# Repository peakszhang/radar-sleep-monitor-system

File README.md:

# radar-sleep-monitor-system
---
## Project description
### Hardware
- ESP32-S-Wroom MCU
- MR60BHA1 60GHz mmWave Radar Module

### Firmware
- Radar serial interface
- Wifi connection
- MQTT protocol
- Alarm sound (optional)

### Software
- Smartphone display data (from MQTT)
- Phone alarm
- ESP32 smartconfig (https://github.com/EspressifApp/EsptouchForAndroid)
- Cloud server (optional)

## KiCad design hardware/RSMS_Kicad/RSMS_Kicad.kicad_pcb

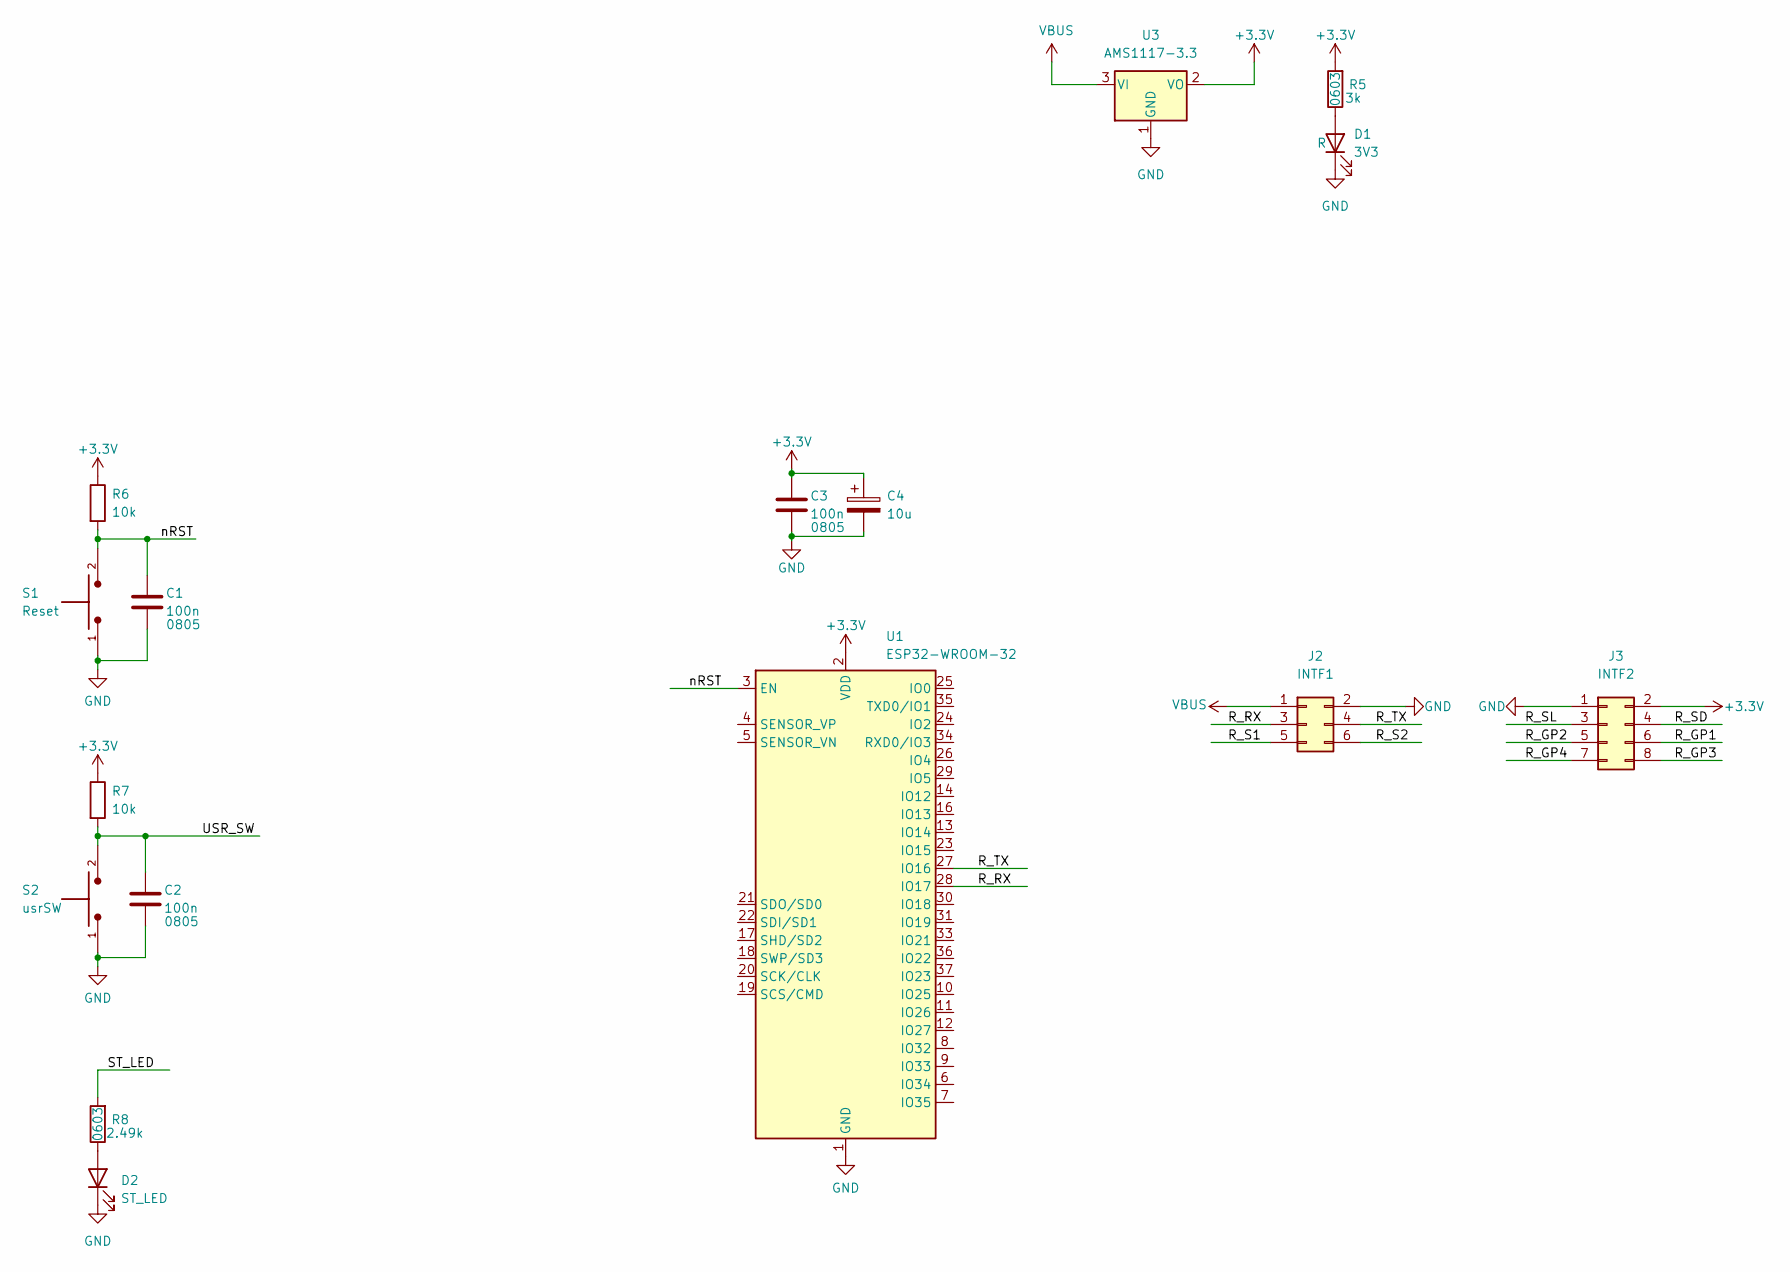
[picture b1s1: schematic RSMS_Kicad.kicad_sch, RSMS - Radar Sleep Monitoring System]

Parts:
C1, C2, C3: 100n; C_0805_2012Metric
C4: 10u; CP_EIA-3216-10_Kemet-I
D1: 3V3; LED_0805_2012Metric
D2: ST_LED; LED_0805_2012Metric
J2: INTF1; PinHeader_2x03_P2.00mm_Vertical_SMD
J3: INTF2; PinSocket_2x04_P2.00mm_Vertical_SMD
R5: 3k; R_0603_1608Metric
R6, R7: 10k; R_0805_2012Metric
R8: 2.49k; R_0603_1608Metric
S1: Reset; SW_TL1015AF160QG; PARTREV F
S2: usrSW; SW_TL1015AF160QG; PARTREV F
U1: ESP32-WROOM-32
U3: AMS1117-3.3; SOT-223-3_TabPin2

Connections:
+3V3: C3.1, C4.1, J3.2, R5.2, R6.1, R7.1, U1.2 (VDD), U3.2 (VO)
/R_GP1: J3.6
/R_GP2: J3.5
/R_GP3: J3.8
/R_GP4: J3.7
/R_RX: J2.3, U1.28 (IO17)
/R_S1: J2.5
/R_S2: J2.6
/R_SD: J3.4
/R_SL: J3.3
/R_TX: J2.4, U1.27 (IO16)
/ST_LED: R8.2
/USR_SW: C2.1, R7.2, S2.2
/nRST: C1.1, R6.2, S1.2, U1.3 (EN)
GND: C1.2, C2.2, C3.2, C4.2, D1.1 (K), D2.1 (K), J2.2, J3.1, S1.1, S2.1, U1.1 (GND), U1.15 (GND), U1.38 (GND), U1.39 (GND), U3.1 (GND)
unnamed: D1.2 (A), R5.1
unnamed: D2.2 (A), R8.1
VBUS: J2.1, U3.3 (VI)

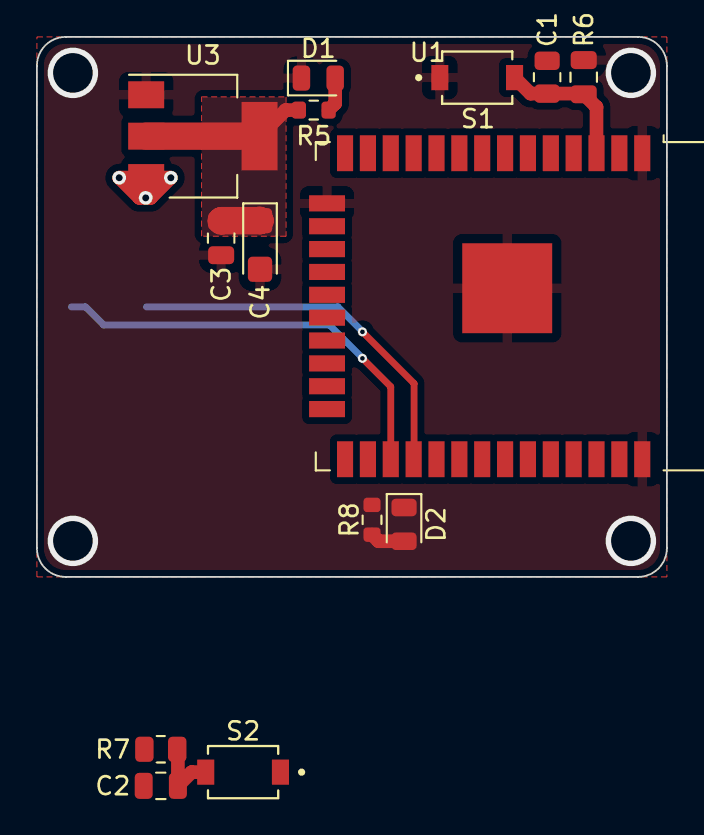
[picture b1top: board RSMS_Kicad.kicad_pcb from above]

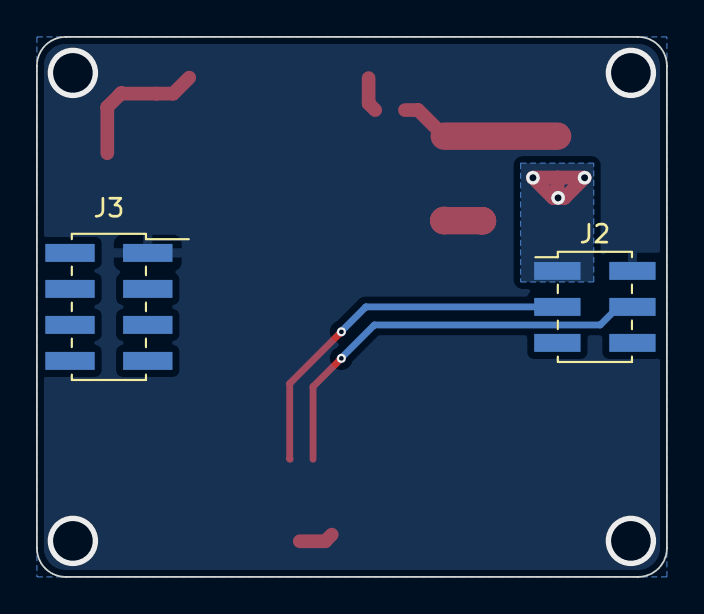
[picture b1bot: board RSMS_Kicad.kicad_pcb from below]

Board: 2 copper layers, 35.0 x 30.0 mm, 16 parts (2 on the bottom side), 9 nets.

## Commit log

2022-09-10 init esp32 firmware project
2022-09-10 update gitignore file
2022-09-10 init: MR60BHA1 driver files
2022-09-19 init hardware kicad project
2022-09-19 add system diagram
2022-09-19 update gitignore
2022-09-19 update project description
2023-03-02 update repo
